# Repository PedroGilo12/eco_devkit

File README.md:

# Projeto de Devkit para a disciplina de Circuitos Impressos

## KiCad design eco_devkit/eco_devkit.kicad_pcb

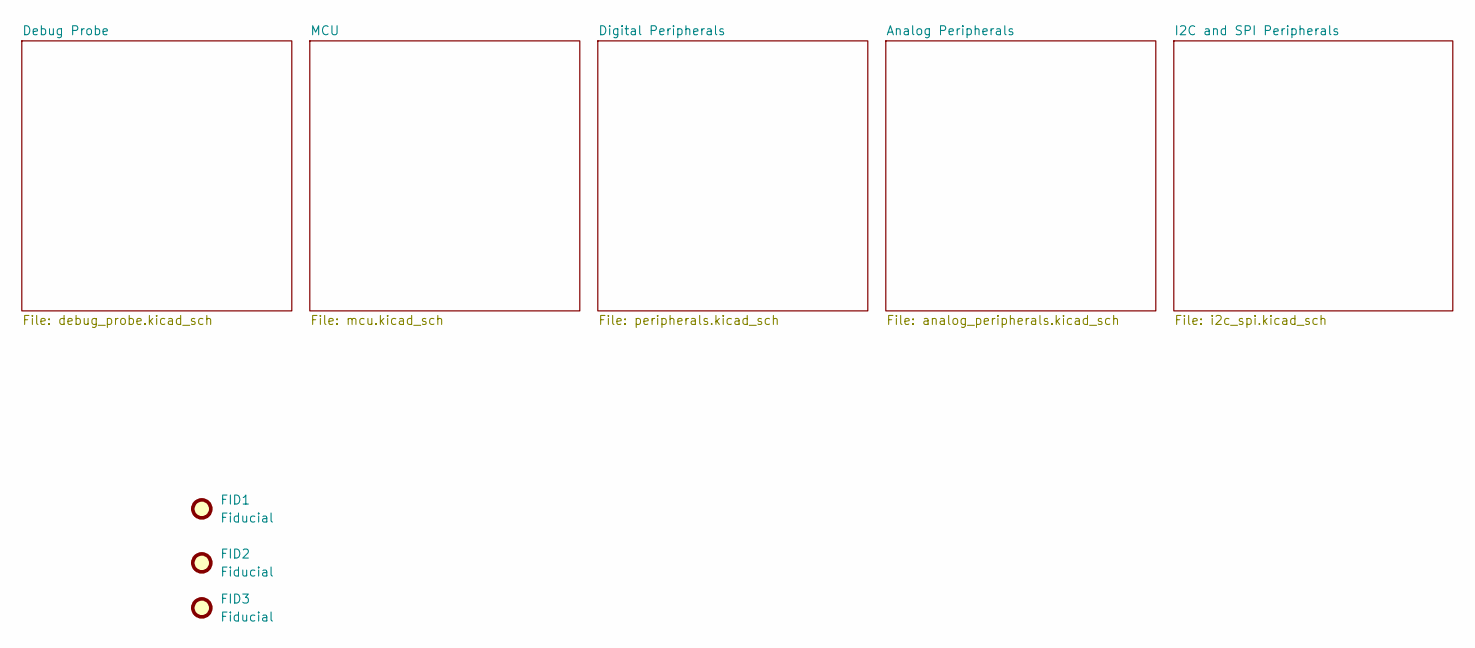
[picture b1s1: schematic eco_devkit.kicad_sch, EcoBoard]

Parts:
FID1, FID2, FID3: Fiducial; Fiducial_1mm_Mask2mm

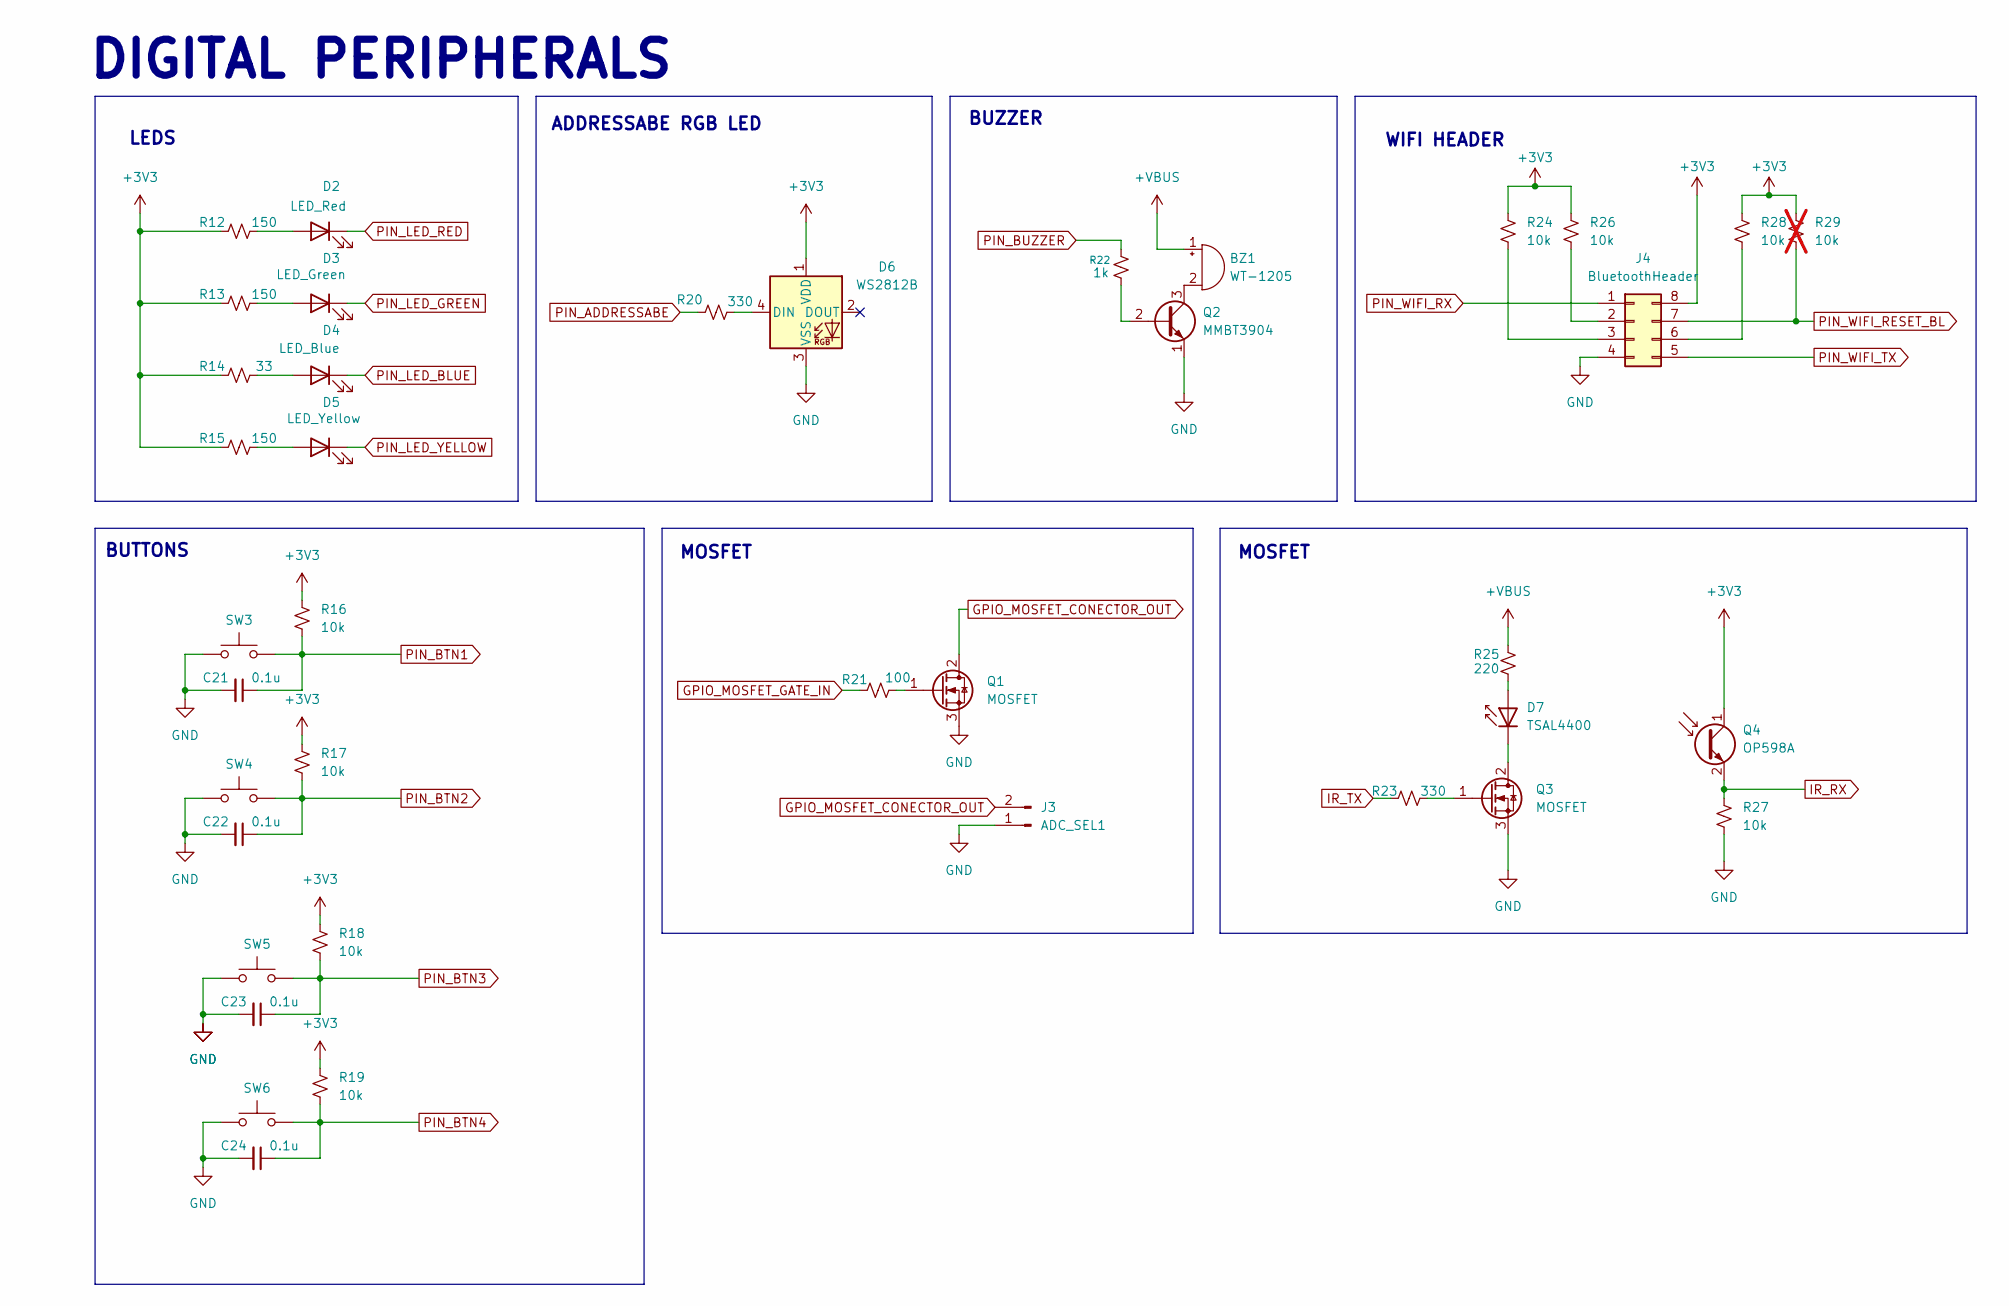
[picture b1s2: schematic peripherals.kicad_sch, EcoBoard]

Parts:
BZ1: WT-1205; buzzer; MPN WT-1205
C21, C22, C23, C24: 0.1u; C_0402_1005Metric; MPN CL05B104KP5VPNC
D2: LED_Red; LED_1206_3216Metric; MPN B1911USD-20D000114U1930
D3: LED_Green; LED_1206_3216Metric; MPN B1931NG--20D001114U1930
D4: LED_Blue; LED_1206_3216Metric; MPN E1221NB--05D000814U1930
D5: LED_Yellow; LED_1206_3216Metric; MPN B1911UYG-20D000114U1930
D6: WS2812B; LED_WS2812B_PLCC4_5.0x5.0mm_P3.2mm; MPN 16347
D7: TSAL4400; LED_D3.0mm_Horizontal_O1.27mm_Z2.0mm; MPN TSAL4400
J3: ADC_SEL1; PinSocket_1x02_P2.54mm_Vertical
J4: BluetoothHeader; PinHeader_2x04_P2.54mm_Vertical
Q1, Q3: MOSFET; SOT-23; MPN PJA3404A_R1_00001
Q2: MMBT3904; SOT-523; MPN MMBT3904TB_R1_00001
Q4: OP598A; LED_D3.0mm_Horizontal_O1.27mm_Z2.0mm_Clear; MPN OP598A
R12, R13, R15: 150; R_0402_1005Metric; MPN CRCW0402150RFKEDHP
R14: 33; R_0402_1005Metric; MPN AC0402FR-7W33RL
R16, R17, R18, R19, R24, R26, R27, R28: 10k; R_0402_1005Metric; MPN CRGP0402F10K
R20, R23: 330; R_0402_1005Metric; MPN CRCW0402330RFKEDHP
R21: 100; R_0402_1005Metric; MPN CRCW0402100RFKEDHP
R22: 1k; R_0402_1005Metric; MPN CRCW04021K00FKED
R25: 220; R_0402_1005Metric; MPN PFR05S-221-FNH
R29: 10k; R_0402_1005Metric; MPN CRGP0402F10K; not fitted
SW3, SW4, SW5, SW6: PTS636; SW_Tactile_SPST_NO_Straight_CK_PTS636Sx25SMTRLFS; MPN PTS636 SK43 SMTR LFS

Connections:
+3V3: D6.1 (VDD), J4.8, Q4.1 (C), R12.2, R13.2, R14.2, R15.2, R16.1, R17.1, R18.1, R19.1, R24.1, R26.1, R28.1, R29.1; also elsewhere on the board
+VBUS: BZ1.1 (+), R25.1; also elsewhere on the board
GND: C21.2, C22.2, C23.2, C24.2, D6.3 (VSS), J3.1, J4.4, Q1.3 (S), Q2.1 (E), Q3.3 (S), R27.2, SW3.1, SW4.1, SW5.1, SW6.1; also elsewhere on the board
GPIO_MOSFET_CONECTOR_OUT: J3.2, Q1.2 (D)
GPIO_MOSFET_GATE_IN: R21.2; also elsewhere on the board
IR_RX: Q4.2 (E), R27.1; also elsewhere on the board
IR_TX: R23.1; also elsewhere on the board
unnamed: BZ1.2 (-), Q2.3 (C)
unnamed: D2.2 (A), R12.1
unnamed: D3.2 (A), R13.1
unnamed: D4.2 (A), R14.1
unnamed: D5.2 (A), R15.1
unnamed: D6.4 (DIN), R20.2
unnamed: D7.2 (A), R25.2
unnamed: D7.1 (K), Q3.2 (D)
unnamed: J4.2, R26.2
unnamed: J4.3, R24.2
unnamed: J4.6, R28.2
unnamed: Q1.1 (G), R21.1
unnamed: Q2.2 (B), R22.1
unnamed: Q3.1 (G), R23.2
PIN_ADDRESSABE: R20.1; also elsewhere on the board
PIN_BTN1: C21.1, R16.2, SW3.2; also elsewhere on the board
PIN_BTN2: C22.1, R17.2, SW4.2; also elsewhere on the board
PIN_BTN3: C23.1, R18.2, SW5.2; also elsewhere on the board
PIN_BTN4: C24.1, R19.2, SW6.2; also elsewhere on the board
PIN_BUZZER: R22.2; also elsewhere on the board
PIN_LED_BLUE: D4.1 (K); also elsewhere on the board
PIN_LED_GREEN: D3.1 (K); also elsewhere on the board
PIN_LED_RED: D2.1 (K); also elsewhere on the board
PIN_LED_YELLOW: D5.1 (K); also elsewhere on the board
PIN_WIFI_RESET_BL: J4.7, R29.2; also elsewhere on the board
PIN_WIFI_RX: J4.1; also elsewhere on the board
PIN_WIFI_TX: J4.5; also elsewhere on the board

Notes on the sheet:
WIFI HEADER
MOSFET
BUTTONS
BUZZER
LEDS
ADDRESSABE RGB LED
DIGITAL PERIPHERALS

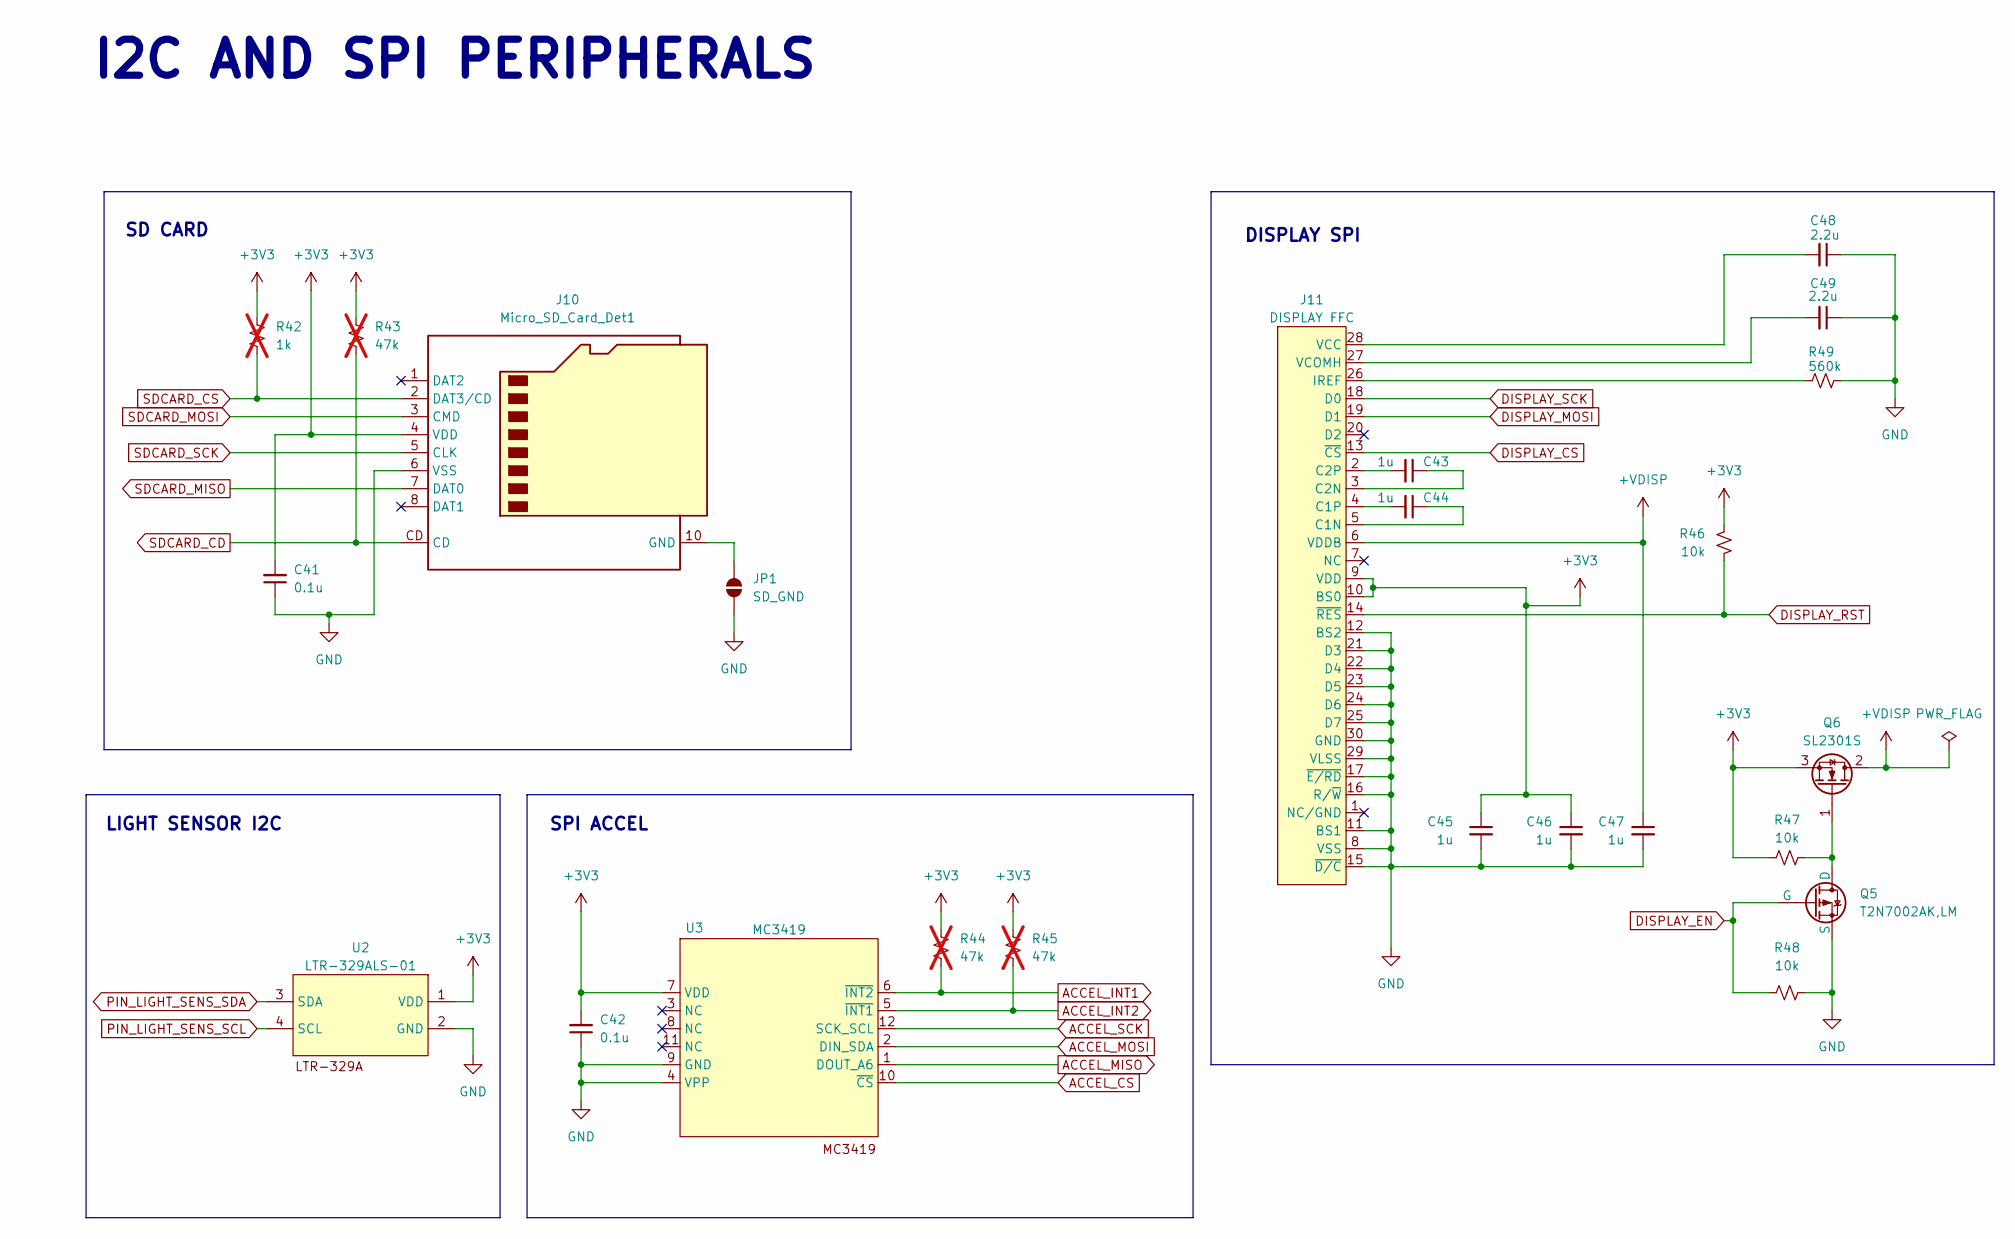
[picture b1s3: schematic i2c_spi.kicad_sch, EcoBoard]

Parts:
C41, C42: 0.1u; C_0402_1005Metric; MPN CL05B104KP5VPNC
C43, C44, C45, C46, C47: 1u; C_0402_1005Metric; MPN C1005X6S1C105K050EC
C48, C49: 2.2u; C_0402_1005Metric; MPN CL05A225KO5NQNC
J10: Micro_SD_Card_Det1; CUI_MSD-4-A; MPN MSD-4-A
J11: DISPLAY FFC; FPC_30; MPN CF4228FH0R0-05-NH
JP1: SD_GND; SolderJumper-2_P1.3mm_Open_TrianglePad1.0x1.5mm
Q5: T2N7002AK,LM; SOT-23-3; MPN T2N7002AK,LM
Q6: SL2301S; SOT-23; MPN SL2301S
R42: 1k; R_0402_1005Metric; MPN CRCW04021K00FKED; not fitted
R43, R44, R45: 47k; R_0402_1005Metric; MPN CRCW040247K0FKEDC; not fitted
R46, R47, R48: 10k; R_0402_1005Metric; MPN CRGP0402F10K
R49: 560k; R_0402_1005Metric; MPN CRGP0402F560K
U2: LTR-329ALS-01; LTR-329ALS-01_LTO; MPN LTR-329ALS-01
U3: MC3419; LGA-12_2x2mm_P0.5mm; MPN MC3419

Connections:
+3V3: C41.2, C42.2, C45.1, C46.1, J10.4 (VDD), J11.9 (VDD), J11.10 (BS0), Q6.3 (S), R42.1, R43.1, R44.1, R45.1, R46.1, R47.1, U2.1 (VDD), U3.7 (VDD); also elsewhere on the board
+VDISP: C47.1, J11.6 (VDDB), Q6.2 (D)
ACCEL_CS: U3.10 (~CS); also elsewhere on the board
ACCEL_INT1: R44.2, U3.6 (~INT2); also elsewhere on the board
ACCEL_INT2: R45.2, U3.5 (~INT1); also elsewhere on the board
DISPLAY_CS: J11.13 (~CS)
DISPLAY_EN: Q5.2 (G), R48.1; also elsewhere on the board
DISPLAY_MOSI: J11.19 (D1); also elsewhere on the board
DISPLAY_RST: J11.14 (~RES), R46.2; also elsewhere on the board
DISPLAY_SCK: J11.18 (D0); also elsewhere on the board
GND: C41.1, C42.1, C45.2, C46.2, C47.2, C48.1, C49.1, J10.6 (VSS), J11.8 (VSS), J11.11 (BS1), J11.12 (BS2), J11.15 (~D/C), J11.16 (R/~W), J11.17 (~E/RD), J11.21 (D3), J11.22 (D4), J11.23 (D5), J11.24 (D6), J11.25 (D7), J11.29 (VLSS), J11.30 (GND), JP1.1 (A), Q5.3 (S), R48.2, R49.1, U2.2 (GND), U3.4 (VPP), U3.9 (GND); also elsewhere on the board
GPIO21: J10.2 (DAT3/CD), R42.2; also elsewhere on the board
GPIO22: J10.CD, R43.2; also elsewhere on the board
unnamed: J10.10 (GND), JP1.2 (B)
unnamed: C44.1, J11.5 (C1N)
unnamed: C44.2, J11.4 (C1P)
unnamed: C43.1, J11.3 (C2N)
unnamed: C43.2, J11.2 (C2P)
unnamed: J11.26 (IREF), R49.2
unnamed: C48.2, J11.28 (VCC)
unnamed: C49.2, J11.27 (VCOMH)
unnamed: Q5.1 (D), Q6.1 (G), R47.2
PIN_LIGHT_SENS_SCL: U2.4 (SCL); also elsewhere on the board
PIN_LIGHT_SENS_SDA: U2.3 (SDA); also elsewhere on the board

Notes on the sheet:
I2C AND SPI PERIPHERALS
DISPLAY SPI
SD CARD
LIGHT SENSOR I2C
SPI ACCEL

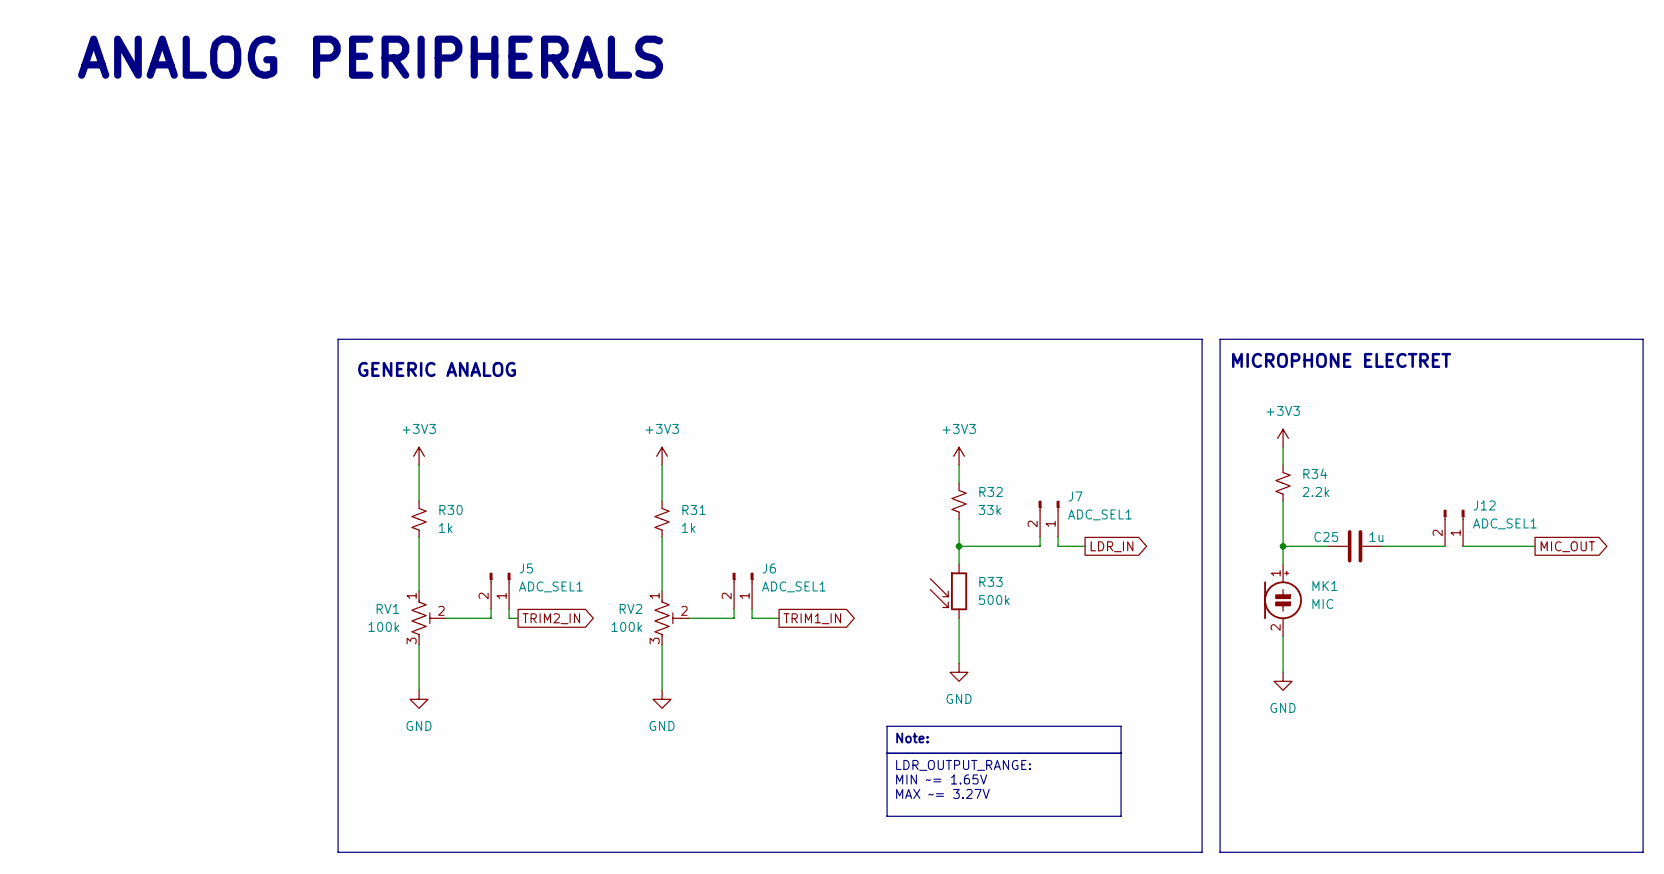
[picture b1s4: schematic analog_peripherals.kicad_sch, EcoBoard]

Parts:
C25: 1u; C_0402_1005Metric; MPN C1005X6S1C105K050EC
J5, J6, J7, J12: ADC_SEL1; PinHeader_1x02_P2.54mm_Vertical
MK1: MIC; MIC_CMEJ-0415-42-P; MPN CMEJ-0415-42-P
R30, R31: 1k; R_0402_1005Metric; MPN CRCW04021K00FKED
R32: 33k; R_0402_1005Metric; MPN CRCW040233K0FKEDC
R33: 500k; R_LDR_5.1x4.3mm_P3.4mm_Vertical; MPN PDV-P8103
R34: 2.2k; R_0402_1005Metric; MPN CRCW04022K20FKED
RV1, RV2: 100k; TRIM_TC33X-2-203E; MPN TC33X-2-104E

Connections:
+3V3: R30.1, R31.1, R32.1, R34.1; also elsewhere on the board
GND: MK1.2 (-), R33.2, RV1.3, RV2.3; also elsewhere on the board
GPIO44_ADC4: J12.1; also elsewhere on the board
GPIO45_ADC5: J6.1; also elsewhere on the board
GPIO46_ADC6: J7.1; also elsewhere on the board
GPIO47_ADC7: J5.1; also elsewhere on the board
unnamed: J5.2, RV1.2
unnamed: J6.2, RV2.2
unnamed: J7.2, R32.2, R33.1
unnamed: C25.2, J12.2
unnamed: C25.1, MK1.1 (+), R34.2
unnamed: R30.2, RV1.1
unnamed: R31.2, RV2.1

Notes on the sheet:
GENERIC ANALOG
MICROPHONE ELECTRET
ANALOG PERIPHERALS
Note:
LDR_OUTPUT_RANGE: MIN ~= 1.65V MAX ~= 3.27V

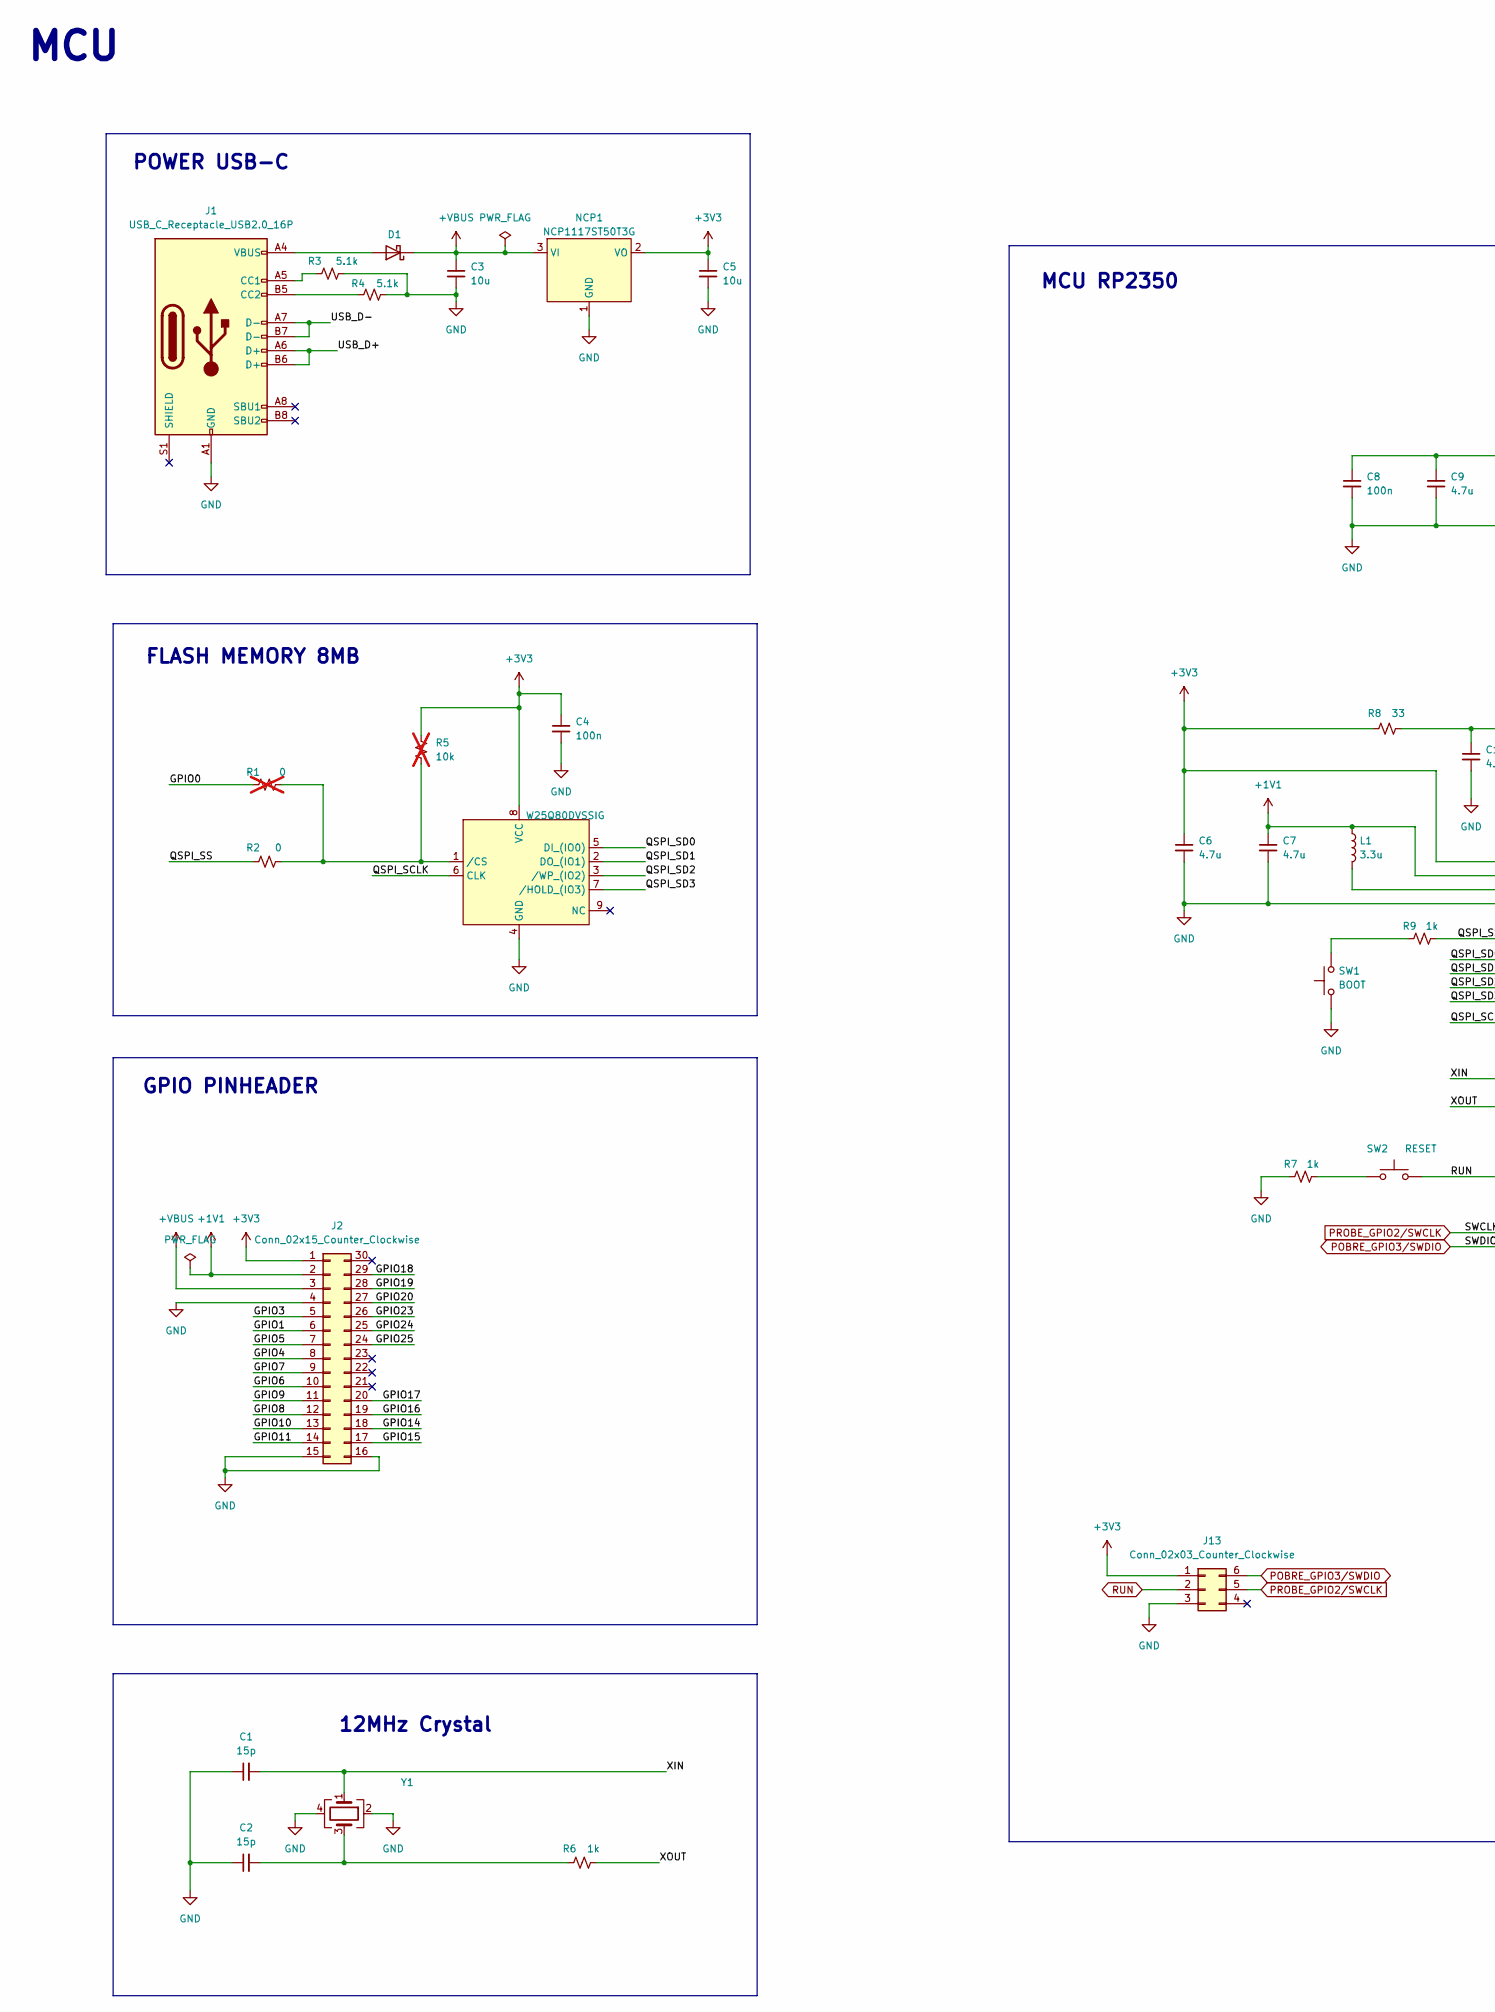
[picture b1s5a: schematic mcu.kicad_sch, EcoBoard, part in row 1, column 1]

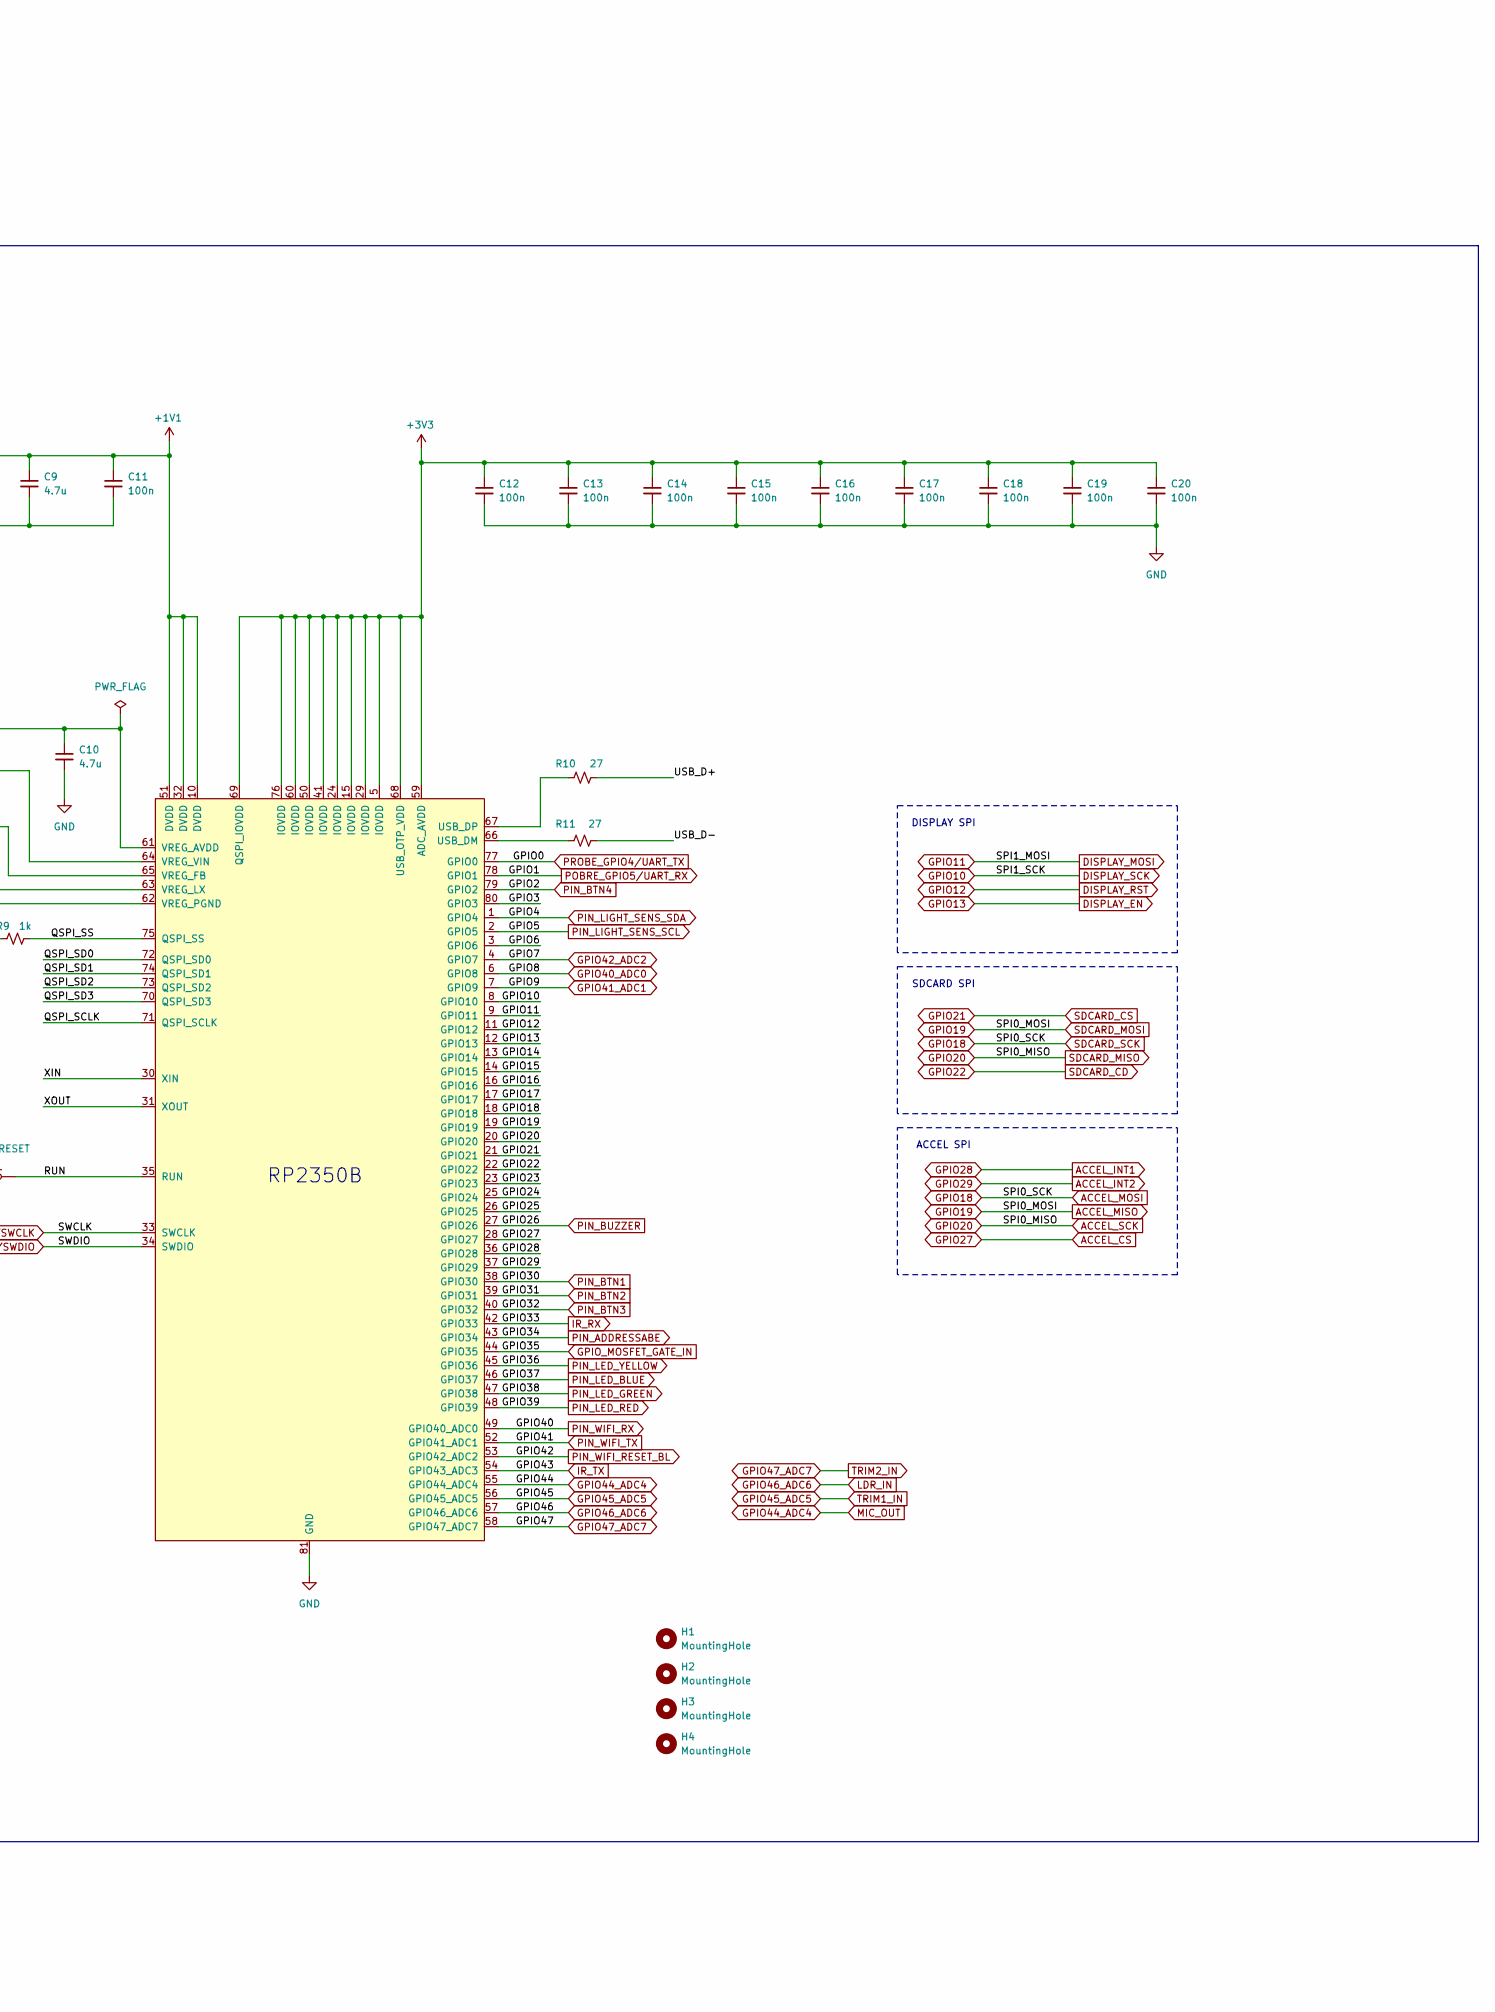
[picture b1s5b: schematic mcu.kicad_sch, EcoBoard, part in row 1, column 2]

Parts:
C1, C2: 15p; C_0402_1005Metric; MPN C0603C150K8RACAUTO
C3, C5: 10u; C_0402_1005Metric; MPN 0402W106M6R3HI
C4, C8, C11, C12, C13, C14, C15, C16, C17, C18, C19, C20: 100n; C_0402_1005Metric; MPN 0402B104K250HI
C6, C7, C9, C10: 4.7u; C_0402_1005Metric; MPN 0402W475M6R3HI
D1: SB120; D_SOD-123F; MPN SM5817PL-TP
FLASH_MEMORY_8MB1: W25Q80DVSSIG; WSON-8-1EP_6x5mm_P1.27mm_EP3.4x4.3mm; MPN W25Q80DVSSIG
H1, H2, H3, H4: MountingHole; MountingHole_2.2mm_M2_DIN965_Pad_TopBottom
J1: USB_C_Receptacle_USB2.0_16P; UJ20-C-H-G-SMT-1-P16-TR; MPN UJ20-C-H-G-SMT-1-P16-TR
J2: Conn_02x15_Counter_Clockwise; PinSocket_2x15_P2.54mm_Vertical
J13: Conn_02x03_Counter_Clockwise; PinHeader_2x03_P2.54mm_Vertical
L1: 3.3u; L_0402_1005Metric; MPN AOTA-B201610S3R3-101-T
NCP1: NCP1117ST50T3G; MPN NCP1117ST50T3G
R1: 0; R_0402_1005Metric; not fitted
R2: 0; R_0402_1005Metric; MPN ERJ-2LWFR010X
R3, R4: 5.1k; R_0402_1005Metric; MPN RC0402FR-7W5K1L
R5: 10k; R_0402_1005Metric; not fitted
R6, R7, R9: 1k; R_0402_1005Metric; MPN CRCW04021K00FKED
R8: 33; R_0402_1005Metric; MPN AC0402FR-7W33RL
R10, R11: 27; R_0402_1005Metric; MPN RCS040227R0FKED
RP2350B1: RP2350B1; RP2350B_QFN-80_EP_10.573x10.573_Pitch0.4mm; MPN SC1510
SW1: BOOT; SW_Tactile_SPST_NO_Straight_CK_PTS636Sx25SMTRLFS; MPN PTS636 SK43 SMTR LFS
SW2: RESET; SW_Tactile_SPST_NO_Straight_CK_PTS636Sx25SMTRLFS; MPN PTS636 SK43 SMTR LFS
Y1: Crystal_GND24; ABM8-272-T3; MPN ABM8-272-T3

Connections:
+1V1: C7.1, C8.1, C9.1, C11.1, J2.2, L1.1, RP2350B1.10 (DVDD), RP2350B1.32 (DVDD), RP2350B1.51 (DVDD), RP2350B1.65 (VREG_FB)
+3V3: C4.1, C5.1, C6.1, C12.1, C13.1, C14.1, C15.1, C16.1, C17.1, C18.1, C19.1, C20.1, FLASH_MEMORY_8MB1.8 (VCC), J2.1, J13.1, NCP1.2 (VO), R5.1, R8.1, RP2350B1.5 (IOVDD), RP2350B1.15 (IOVDD), RP2350B1.24 (IOVDD), RP2350B1.29 (IOVDD), RP2350B1.41 (IOVDD), RP2350B1.50 (IOVDD), RP2350B1.59 (ADC_AVDD), RP2350B1.60 (IOVDD), RP2350B1.64 (VREG_VIN), RP2350B1.68 (USB_OTP_VDD), RP2350B1.69 (QSPI_IOVDD), RP2350B1.76 (IOVDD); also elsewhere on the board
+VBUS: C3.1, D1.1 (K), J2.3, NCP1.3 (VI); also elsewhere on the board
/MCU/GPIO3: J2.5, RP2350B1.80 (GPIO3)
/MCU/GPIO6: J2.10, RP2350B1.3 (GPIO6)
/MCU/GPIO14: J2.18, RP2350B1.13 (GPIO14)
/MCU/GPIO15: J2.17, RP2350B1.14 (GPIO15)
/MCU/GPIO16: J2.19, RP2350B1.16 (GPIO16)
/MCU/GPIO17: J2.20, RP2350B1.17 (GPIO17)
/MCU/GPIO23: J2.26, RP2350B1.23 (GPIO23)
/MCU/GPIO24: J2.25, RP2350B1.25 (GPIO24)
/MCU/GPIO25: J2.24, RP2350B1.26 (GPIO25)
/MCU/QSPI_SCLK: FLASH_MEMORY_8MB1.6 (CLK), RP2350B1.71 (QSPI_SCLK)
/MCU/QSPI_SD0: FLASH_MEMORY_8MB1.5 (DI_(IO0)), RP2350B1.72 (QSPI_SD0)
/MCU/QSPI_SD1: FLASH_MEMORY_8MB1.2 (DO_(IO1)), RP2350B1.74 (QSPI_SD1)
/MCU/QSPI_SD2: FLASH_MEMORY_8MB1.3 (/WP_(IO2)), RP2350B1.73 (QSPI_SD2)
/MCU/QSPI_SD3: FLASH_MEMORY_8MB1.7 (/HOLD_(IO3)), RP2350B1.70 (QSPI_SD3)
/MCU/QSPI_SS: R2.1, R9.2, RP2350B1.75 (QSPI_SS)
/MCU/USB_D+: J1.A6 (D+), J1.B6 (D+), R10.2
/MCU/USB_D-: J1.A7 (D-), J1.B7 (D-), R11.2
/MCU/XIN: C1.2, RP2350B1.30 (XIN), Y1.1
/MCU/XOUT: R6.2, RP2350B1.31 (XOUT)
ACCEL_CS: RP2350B1.28 (GPIO27); also elsewhere on the board
ACCEL_INT1: RP2350B1.36 (GPIO28); also elsewhere on the board
ACCEL_INT2: RP2350B1.37 (GPIO29); also elsewhere on the board
DISPLAY_EN: RP2350B1.12 (GPIO13); also elsewhere on the board
DISPLAY_MOSI: J2.14, RP2350B1.9 (GPIO11); also elsewhere on the board
DISPLAY_RST: RP2350B1.11 (GPIO12); also elsewhere on the board
DISPLAY_SCK: J2.13, RP2350B1.8 (GPIO10); also elsewhere on the board
GND: C1.1, C2.1, C3.2, C4.2, C5.2, C6.2, C7.2, C8.2, C9.2, C10.2, C11.2, C12.2, C13.2, C14.2, C15.2, C16.2, C17.2, C18.2, C19.2, C20.2, FLASH_MEMORY_8MB1.4 (GND), J1.A1 (GND), J1.A12 (GND), J1.B1 (GND), J1.B12 (GND), J2.4, J2.15, J2.16, J13.3, NCP1.1 (GND), R3.2, R4.2, R7.1, RP2350B1.62 (VREG_PGND), RP2350B1.81 (GND), SW1.1, Y1.2, Y1.4; also elsewhere on the board
GPIO21: RP2350B1.21 (GPIO21); also elsewhere on the board
GPIO22: RP2350B1.22 (GPIO22); also elsewhere on the board
GPIO40_ADC0: J2.12, RP2350B1.6 (GPIO8)
GPIO41_ADC1: J2.11, RP2350B1.7 (GPIO9)
GPIO42_ADC2: J2.9, RP2350B1.4 (GPIO7)
GPIO44_ADC4: RP2350B1.55 (GPIO44_ADC4); also elsewhere on the board
GPIO45_ADC5: RP2350B1.56 (GPIO45_ADC5); also elsewhere on the board
GPIO46_ADC6: RP2350B1.57 (GPIO46_ADC6); also elsewhere on the board
GPIO47_ADC7: RP2350B1.58 (GPIO47_ADC7); also elsewhere on the board
GPIO_MOSFET_GATE_IN: RP2350B1.44 (GPIO35); also elsewhere on the board
IR_RX: RP2350B1.42 (GPIO33); also elsewhere on the board
IR_TX: RP2350B1.54 (GPIO43_ADC3); also elsewhere on the board
unnamed: C2.2, R6.1, Y1.3
unnamed: D1.2 (A), J1.A4 (VBUS), J1.A9 (VBUS), J1.B4 (VBUS), J1.B9 (VBUS)
unnamed: FLASH_MEMORY_8MB1.1 (/CS), R1.2, R2.2, R5.2
unnamed: J1.A5 (CC1), R3.1
unnamed: J1.B5 (CC2), R4.1
unnamed: R7.2, SW2.1
unnamed: R9.1, SW1.2
unnamed: R11.1, RP2350B1.66 (USB_DM)
unnamed: R10.1, RP2350B1.67 (USB_DP)
unnamed: C10.1, R8.2, RP2350B1.61 (VREG_AVDD)
unnamed: L1.2, RP2350B1.63 (VREG_LX)
PIN_ADDRESSABE: RP2350B1.43 (GPIO34); also elsewhere on the board
PIN_BTN1: RP2350B1.38 (GPIO30); also elsewhere on the board
PIN_BTN2: RP2350B1.39 (GPIO31); also elsewhere on the board
PIN_BTN3: RP2350B1.40 (GPIO32); also elsewhere on the board
PIN_BTN4: RP2350B1.79 (GPIO2); also elsewhere on the board
PIN_BUZZER: RP2350B1.27 (GPIO26); also elsewhere on the board
PIN_LED_BLUE: RP2350B1.46 (GPIO37); also elsewhere on the board
PIN_LED_GREEN: RP2350B1.47 (GPIO38); also elsewhere on the board
PIN_LED_RED: RP2350B1.48 (GPIO39); also elsewhere on the board
PIN_LED_YELLOW: RP2350B1.45 (GPIO36); also elsewhere on the board
PIN_LIGHT_SENS_SCL: J2.7, RP2350B1.2 (GPIO5); also elsewhere on the board
PIN_LIGHT_SENS_SDA: J2.8, RP2350B1.1 (GPIO4); also elsewhere on the board
PIN_WIFI_RESET_BL: RP2350B1.53 (GPIO42_ADC2); also elsewhere on the board
PIN_WIFI_RX: RP2350B1.49 (GPIO40_ADC0); also elsewhere on the board
PIN_WIFI_TX: RP2350B1.52 (GPIO41_ADC1); also elsewhere on the board
POBRE_GPIO3/SWDIO: J13.6, RP2350B1.34 (SWDIO); also elsewhere on the board
POBRE_GPIO5/UART_RX: J2.6, RP2350B1.78 (GPIO1); also elsewhere on the board
PROBE_GPIO2/SWCLK: J13.5, RP2350B1.33 (SWCLK); also elsewhere on the board
PROBE_GPIO4/UART_TX: R1.1, RP2350B1.77 (GPIO0); also elsewhere on the board
RUN: J13.2, RP2350B1.35 (RUN), SW2.2

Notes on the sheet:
GPIO PINHEADER
POWER USB-C
12MHz Crystal
RP2350B
ACCEL SPI
MCU
MCU RP2350
FLASH MEMORY 8MB
DISPLAY SPI
SDCARD SPI
